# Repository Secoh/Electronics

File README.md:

# Electronics
Educational etudes related to electronics, schematics, PCB layout, etc.

Fairly random collection of designs related to my hobbies, with backup in hidden agenda.
Historic items are in PCB123 (private vendor-specific, incompatible with anything else); more recent work is KiCad and LtSpice.

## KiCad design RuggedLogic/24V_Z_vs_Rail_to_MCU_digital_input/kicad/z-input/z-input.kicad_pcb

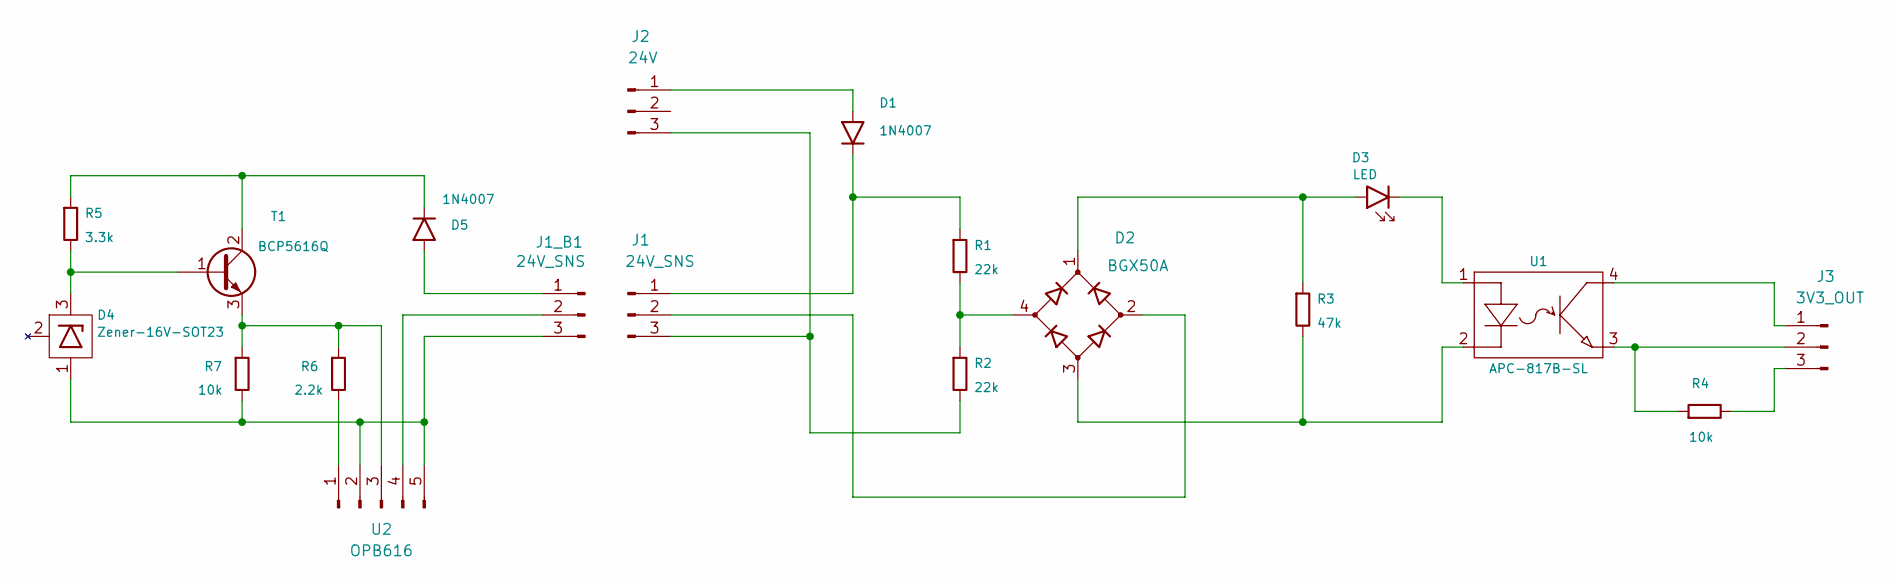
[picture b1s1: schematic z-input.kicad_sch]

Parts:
D1, D5: 1N4007; D_SOD-123F_hand_soldering
D2: BGX50A; SOT-143_Handsoldering
D3: LED; LED_0805
D4: Zener-16V-SOT23; SOT-23_Handsoldering
J1, J1_B1: 24V_SNS; Molex_KK-396_A-41791-0003_1x03_P3.96mm_Vertical
J2: 24V; Molex_KK-396_A-41791-0003_1x03_P3.96mm_Vertical
J3: 3V3_OUT; PinHeader_1x03_P2.54mm_Vertical
R1, R2: 22k; R_0805_2012Metric_Pad1.20x1.40mm_HandSolder
R3: 47k; R_0805_2012Metric_Pad1.20x1.40mm_HandSolder
R4, R7: 10k; R_0805_2012Metric_Pad1.20x1.40mm_HandSolder
R5: 3.3k; R_0805_2012Metric_Pad1.20x1.40mm_HandSolder
R6: 2.2k; R_0805_2012Metric_Pad1.20x1.40mm_HandSolder
T1: BCP5616Q; SOT-223-3_TabPin2
U1: APC-817B-SL; APC-817-SL
U2: OPB616; OPB-616

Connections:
unnamed: D1.2 (A), J2.1
unnamed: D1.1 (K), J1.1, R1.1
unnamed: D2.1 (+), D3.2 (A), R3.1
unnamed: D2.3 (-), R3.2, U1.2 (D-)
unnamed: D2.4, R1.2, R2.1
unnamed: D3.1 (K), U1.1 (D+)
unnamed: D4.1 (A), J1_B1.3, R7.2, U2.2, U2.5
unnamed: D4.3 (K), R5.2, T1.1 (B)
unnamed: D5.2 (A), J1_B1.1
unnamed: D5.1 (K), R5.1, T1.2 (C)
unnamed: D2.2, J1.2
unnamed: J1.3, J2.3, R2.2
unnamed: J1_B1.2, U2.4
unnamed: J3.1, U1.4 (C)
unnamed: J3.2, R4.1, U1.3 (C)
unnamed: J3.3, R4.2
unnamed: R6.1, R7.1, T1.3 (E), U2.3
unnamed: R6.2, U2.1

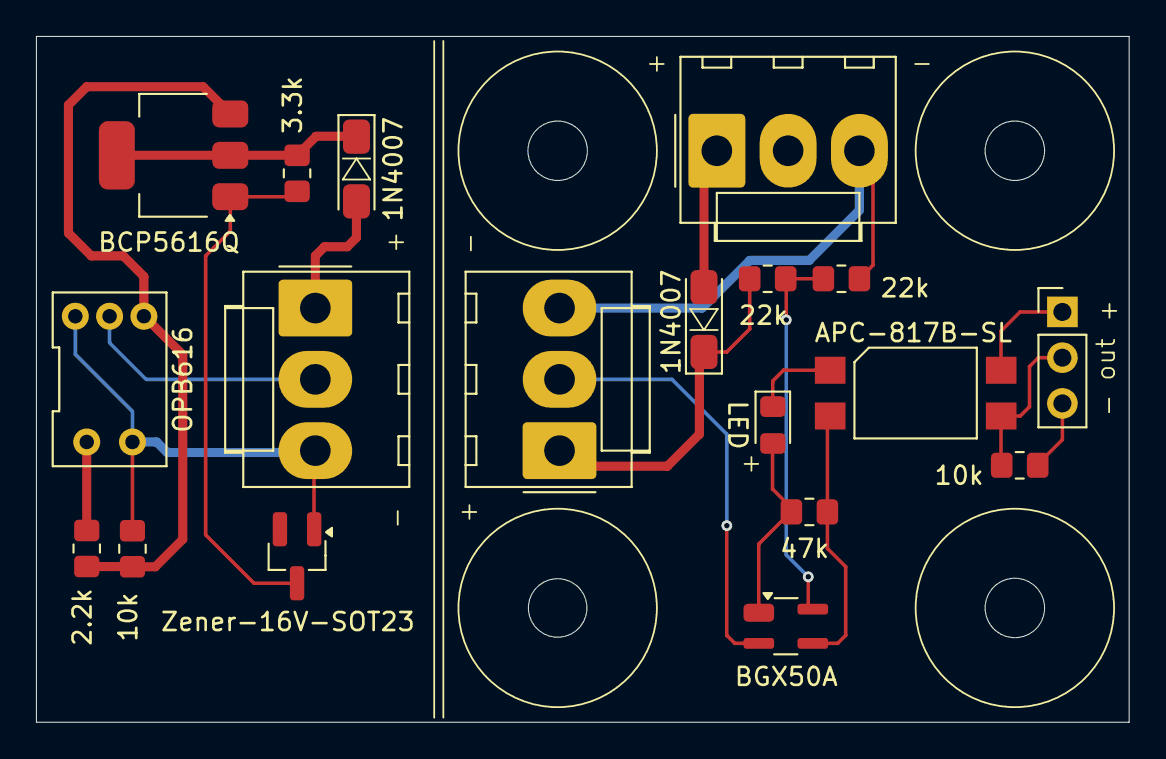
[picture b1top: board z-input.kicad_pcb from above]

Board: 2 copper layers, 60.7 x 38.1 mm, 19 parts (0 on the bottom side), 18 nets.

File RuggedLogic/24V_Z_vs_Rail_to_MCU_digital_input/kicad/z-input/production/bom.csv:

Designator,Footprint,Quantity,Value,LCSC Part #
"D1, D5",D_SOD-123F_hand_soldering,2,1N4007,
D2,SOT-143_Handsoldering,1,BGX50A,
D3,LED_0805,1,LED,
D4,SOT-23_Handsoldering,1,Zener-16V-SOT23,
"J1, J1_B1",Molex_KK-396_A-41791-0003_1x03_P3.96mm_Vertical,2,24V_SNS,
J2,Molex_KK-396_A-41791-0003_1x03_P3.96mm_Vertical,1,24V,
J3,PinHeader_1x03_P2.54mm_Vertical,1,3V3_OUT,
"R1, R2",0805,2,22k,
R3,0805,1,47k,
"R4, R7",0805,2,10k,
R5,0805,1,3.3k,
R6,0805,1,2.2k,
T1,SOT-223-3_TabPin2,1,BCP5616Q,
U1,APC-817-SL,1,APC-817B-SL,
U2,OPB-616,1,OPB616,

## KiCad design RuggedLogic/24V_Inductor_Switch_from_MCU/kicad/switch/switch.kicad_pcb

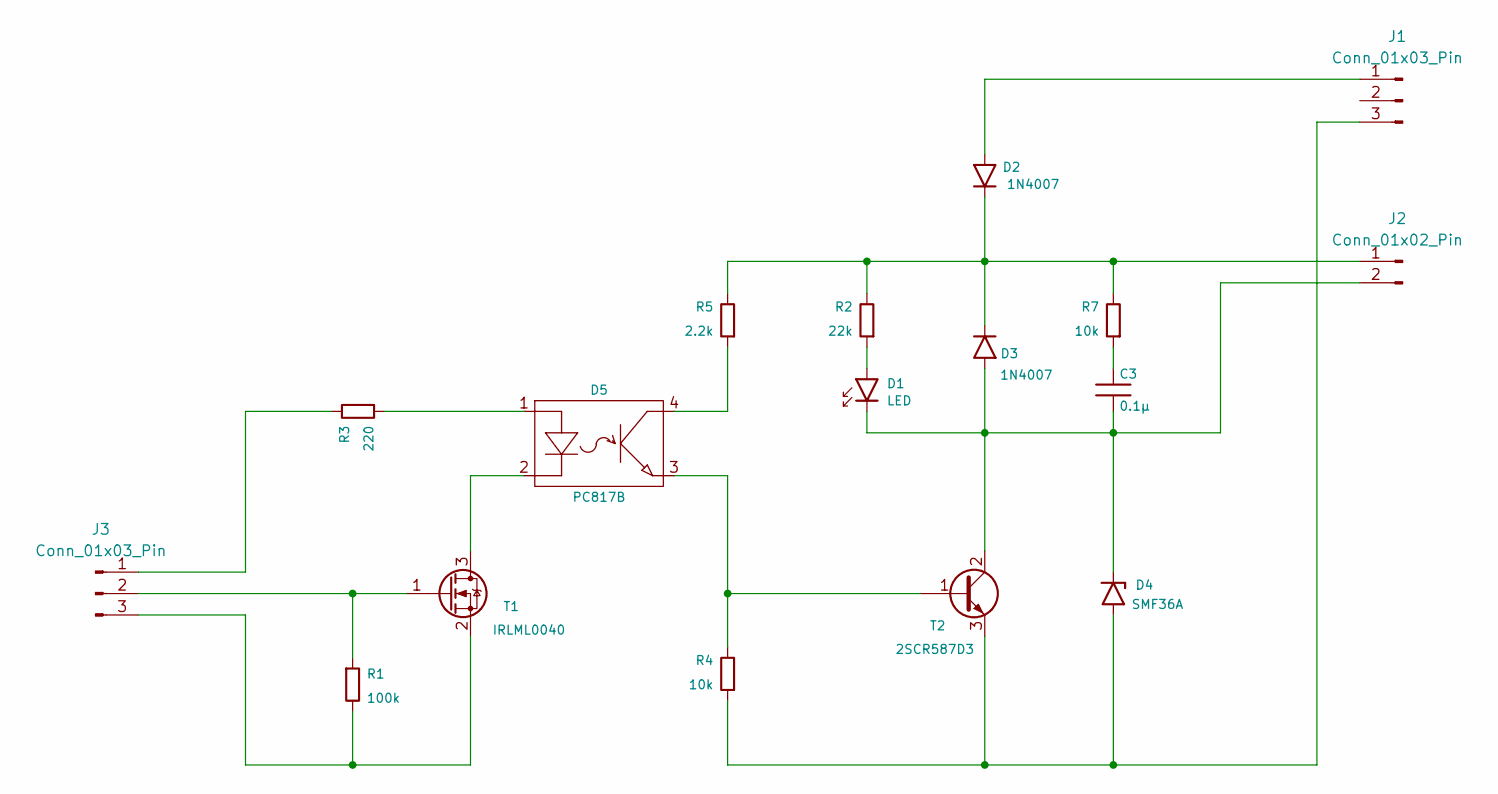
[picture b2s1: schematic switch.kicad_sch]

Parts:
C3: 0.1µ; C_0805_2012Metric_Pad1.18x1.45mm_HandSolder
D1: LED; LED_0805
D2, D3: 1N4007; D_SOD-123F_hand_soldering
D4: SMF36A; D_SOD-123F_hand_soldering
D5: PC817B; APC-817-SL
J1: Conn_01x03_Pin; Molex_KK-396_A-41791-0003_1x03_P3.96mm_Vertical
J2: Conn_01x02_Pin; Molex_KK-396_A-41791-0002_1x02_P3.96mm_Vertical
J3: Conn_01x03_Pin; PinHeader_1x03_P2.54mm_Vertical
R1: 100k; R_0805_2012Metric_Pad1.20x1.40mm_HandSolder
R2: 22k; R_0805_2012Metric_Pad1.20x1.40mm_HandSolder
R3: 220; R_0805_2012Metric_Pad1.20x1.40mm_HandSolder
R4, R7: 10k; R_0805_2012Metric_Pad1.20x1.40mm_HandSolder
R5: 2.2k; R_0805_2012Metric_Pad1.20x1.40mm_HandSolder
T1: IRLML0040; SOT-23_Handsoldering
T2: 2SCR587D3; TO-252-2

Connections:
unnamed: C3.1, R7.1
unnamed: D1.2 (A), R2.1
unnamed: C3.2, D1.1 (K), D3.2 (A), D4.1 (K), J2.2, T2.2 (C)
unnamed: D2.2 (A), J1.1
unnamed: D2.1 (K), D3.1 (K), J2.1, R2.2, R5.2, R7.2
unnamed: D4.2 (A), J1.3, R4.1, T2.3 (E)
unnamed: D5.4 (C), R5.1
unnamed: D5.1 (D+), R3.1
unnamed: D5.2 (D-), T1.3 (D)
unnamed: J3.1, R3.2
unnamed: J3.2, R1.1, T1.1 (G)
unnamed: J3.3, R1.2, T1.2 (S)
unnamed: D5.3 (C), R4.2, T2.1 (B)

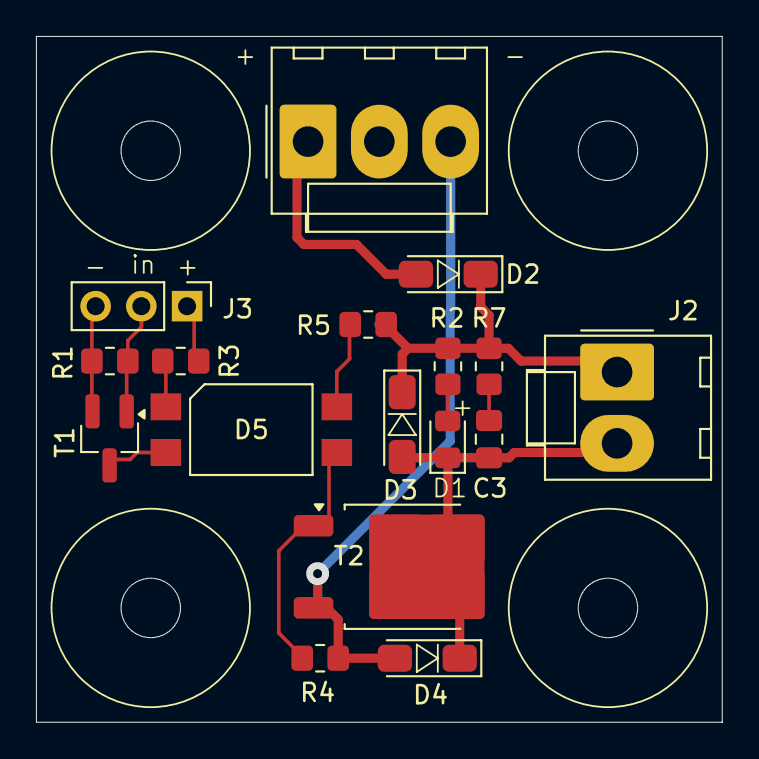
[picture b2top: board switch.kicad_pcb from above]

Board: 2 copper layers, 38.1 x 38.1 mm, 17 parts (0 on the bottom side), 13 nets.

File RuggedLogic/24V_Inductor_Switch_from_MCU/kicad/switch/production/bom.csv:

Designator,Footprint,Quantity,Value,LCSC Part #
C3,0805,1,0.1µ,
D1,LED_0805,1,LED,
"D2, D3",D_SOD-123F_hand_soldering,2,1N4007,
D4,D_SOD-123F_hand_soldering,1,SMF36A,
D5,APC-817-SL,1,PC817B,
J1,Molex_KK-396_A-41791-0003_1x03_P3.96mm_Vertical,1,Conn_01x03_Pin,
J2,Molex_KK-396_A-41791-0002_1x02_P3.96mm_Vertical,1,Conn_01x02_Pin,
J3,PinHeader_1x03_P2.54mm_Vertical,1,Conn_01x03_Pin,
R1,0805,1,100k,
R2,0805,1,22k,
R3,0805,1,220,
"R4, R7",0805,2,10k,
R5,0805,1,2.2k,
T1,SOT-23_Handsoldering,1,IRLML0040,
T2,TO-252-2,1,2SCR587D3,

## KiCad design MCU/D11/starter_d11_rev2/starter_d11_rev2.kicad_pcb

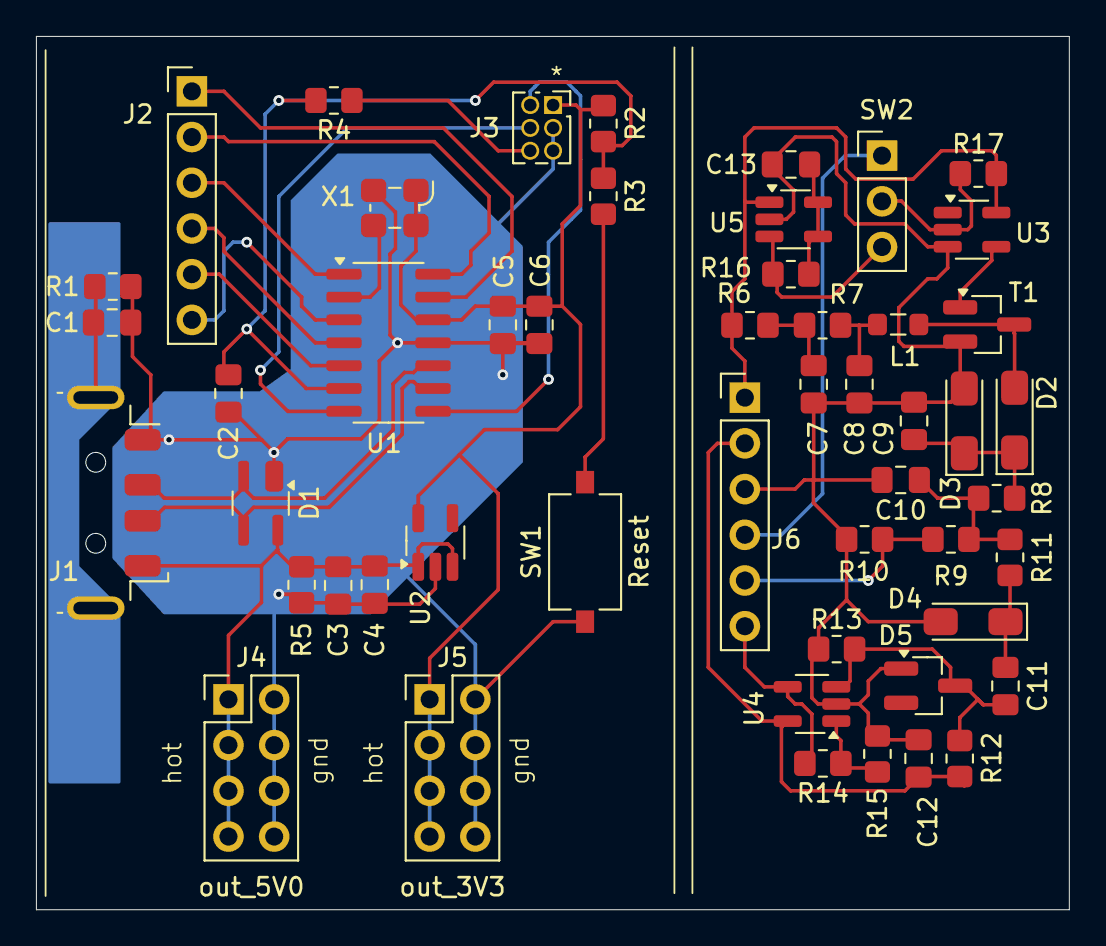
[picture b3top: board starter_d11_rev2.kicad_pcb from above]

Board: 2 copper layers, 57.4 x 48.5 mm, 52 parts (1 on the bottom side), 36 nets.

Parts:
C1, C2: 4.7n; C_0805_2012Metric_Pad1.18x1.45mm_HandSolder
C3, C6: 100n; C_0805_2012Metric_Pad1.18x1.45mm_HandSolder
C4, C5: 4.7u; C_0805_2012Metric_Pad1.18x1.45mm_HandSolder
C7, C8, C13: 2.2µ; C_0805_2012Metric_Pad1.18x1.45mm_HandSolder
C9, C10: 1µ; C_0805_2012Metric_Pad1.18x1.45mm_HandSolder
C11: 0.01µ; C_0805_2012Metric_Pad1.18x1.45mm_HandSolder
C12: 0.1µ; C_0805_2012Metric_Pad1.18x1.45mm_HandSolder
D1: PRTR5V0; SOT-143_Handsoldering
D2: 1N4007; D_SOD-123F_hand_soldering
D3: SMF36A; D_SOD-123F_hand_soldering
D4: SMF24A; D_SOD-123F_hand_soldering
D5: MMBZ5222BLT1G; SOT-23_Handsoldering
J1: USB_A; USB_A_Molex_48037-2200_Horizontal
J1A: USB; pad_single_005x036in_for_USB_A
J2, J6: Conn_01x06_Pin; PinHeader_1x06_P2.54mm_Vertical
J3: SWD-5; PinSocket_2x03_P1.27mm_Vertical
J4: out_5V0; PinHeader_2x04_P2.54mm_Vertical
J5: out_3V3; PinHeader_2x04_P2.54mm_Vertical
L1: 100µ; L_0805_2012Metric_Pad1.05x1.20mm_HandSolder
R1, R5: 1M; R_0805_2012Metric_Pad1.20x1.40mm_HandSolder
R2, R9, R11, R14, R17: 100k; R_0805_2012Metric_Pad1.20x1.40mm_HandSolder
R3, R4: 39; R_0805_2012Metric_Pad1.20x1.40mm_HandSolder
R6, R7: 33; R_0805_2012Metric_Pad1.20x1.40mm_HandSolder
R8, R10, R15: 10k; R_0805_2012Metric_Pad1.20x1.40mm_HandSolder
R12: 1Meg; R_0805_2012Metric_Pad1.20x1.40mm_HandSolder
R13: 47k; R_0805_2012Metric_Pad1.20x1.40mm_HandSolder
R16: 180; R_0805_2012Metric_Pad1.20x1.40mm_HandSolder
SW1: Reset; SW_Tactile_SPST_NO_Straight_CK_PTS636Sx25SMTRLFS
SW2: Conn_01x03_Pin; PinHeader_1x03_P2.54mm_Vertical
T1: 2N7002; SOT-23_Handsoldering
U1: ATSAMD11C14A-SS; SOIC-14_3.9x8.7mm_P1.27mm
U2: TLV73333/SOT-23; SOT-23-5_HandSoldering
U3: MC74VHC1GT14; SOT-23-5_HandSoldering
U4: MAX4230; SOT-23-5_HandSoldering
U5: MIC1555; SOT-23-5_HandSoldering
X1: ECS-2520MV-xxx-xx; ECS-2520MV

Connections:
3V3: C5.1, C6.1, J3.1, J5.1, J5.3, J5.5, J5.7, R2.1, U1.12 (VDD), U2.5 (3V3), X1.1 (Tri-State), X1.4 (VDD)
3V3-1: C12.1, J6.2, R12.1, U4.5 (V+)
5V0: C3.1, C4.1, D1.4 (Vcc), J1.1 (VBUS), J4.1, J4.3, J4.5, J4.7, R5.1, U2.1 (IN), U2.3 (EN)
5V0-1: J6.1, R6.2, R17.2, U3.5 (VCC), U5.1 (VCC)
/Inset A - USB MCU/CLK: U1.2 (PA08/XIN), X1.3 (OUT)
/Inset A - USB MCU/RST: C2.1, R2.2, R3.1, R4.2, U1.6 (PA28/~RST)
/Inset A - USB MCU/SWCLK: J3.4, U1.7 (PA30/SWCLK)
/Inset A - USB MCU/SWDIO: J3.2, U1.8 (PA31/SWDIO)
/Inset A - USB MCU/Shield: C1.1, J1.5 (Shield), J1A.1, R1.1
/Inset A - USB MCU/USB-M: D1.3, J1.2 (D-), U1.9 (PA24)
/Inset A - USB MCU/USB-P: D1.2, J1.3 (D+), U1.10 (PA25)
DRV: J6.4, SW2.1
GEN: J6.6, R14.2, U4.4
GND: C1.2, C2.2, C3.2, C4.2, C5.2, C6.2, D1.1 (Gnd), J1.4 (GND), J3.3, J3.5, J4.2, J4.4, J4.6, J4.8, J5.2, J5.4, J5.6, J5.8, R1.2, R5.2, SW1.1, U1.11 (GND), U2.2 (GND), X1.2 (GND)
GND1: C7.2, C8.2, C9.2, C10.2, C12.2, C13.2, D3.2 (A), D4.2 (A), D5.1 (A), J6.3, R10.1, R13.1, R15.2, T1.2 (S), U3.3 (GND), U4.2 (V-), U5.2 (GND)
unnamed: C7.1, R6.1, R7.2
unnamed: C8.1, L1.1, R7.1
unnamed: C10.1, R8.1, R9.2, R11.2
unnamed: D2.2 (A), L1.2, T1.3 (D)
unnamed: C9.1, D2.1 (K), D3.1 (K), R8.2
unnamed: C11.2, D4.1 (K), R11.1
unnamed: C11.1, D5.3 (K), R12.2, R13.2, U4.3 (-)
unnamed: J2.1, U1.13 (PA02)
unnamed: J2.2, U1.14 (PA04)
unnamed: J2.3, U1.1 (PA05)
unnamed: J2.4, U1.4 (PA14)
unnamed: J2.5, U1.5 (PA15)
unnamed: J2.6, U1.3 (PA09/XOUT)
unnamed: J3.6, R4.1
unnamed: R3.2, SW1.2
unnamed: R17.1, SW2.2, U3.2
unnamed: R16.1, SW2.3, U5.3 (OUT)
unnamed: T1.1 (G), U3.4
unnamed: R14.1, R15.1, U4.1 (+)
unnamed: C13.1, R16.2, U5.4 (TRG), U5.5 (THR)
RDY: J6.5, R9.1, R10.2

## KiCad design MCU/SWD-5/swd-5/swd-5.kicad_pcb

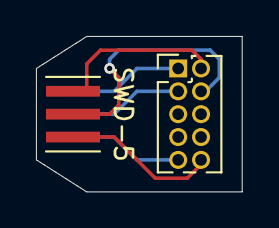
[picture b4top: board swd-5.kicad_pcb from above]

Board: 2 copper layers, 11.4 x 8.6 mm, 3 parts (1 on the bottom side), 6 nets.

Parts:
J1-A1, J1-B1: SWD-5; conn_edge_hdr_pin_3_spc_1.27
J2: SWD-10; PinHeader_2x05_P1.27mm_Vertical

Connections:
/GND: J1-A1.2, J2.3
/GND2: J1-A1.3, J2.9
/RST: J1-B1.3, J2.10
/SWCLK: J1-B1.2, J2.4
/SWDIO: J1-B1.1, J2.2
/VCC: J1-A1.1, J2.1

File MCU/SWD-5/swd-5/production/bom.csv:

Designator,Footprint,Quantity,Value,LCSC Part #
"J1-A1, J1-B1",conn_edge_hdr_pin_3_spc_1.27,2,SWD-5,
J2,PinHeader_2x05_P1.27mm_Vertical,1,SWD-10,

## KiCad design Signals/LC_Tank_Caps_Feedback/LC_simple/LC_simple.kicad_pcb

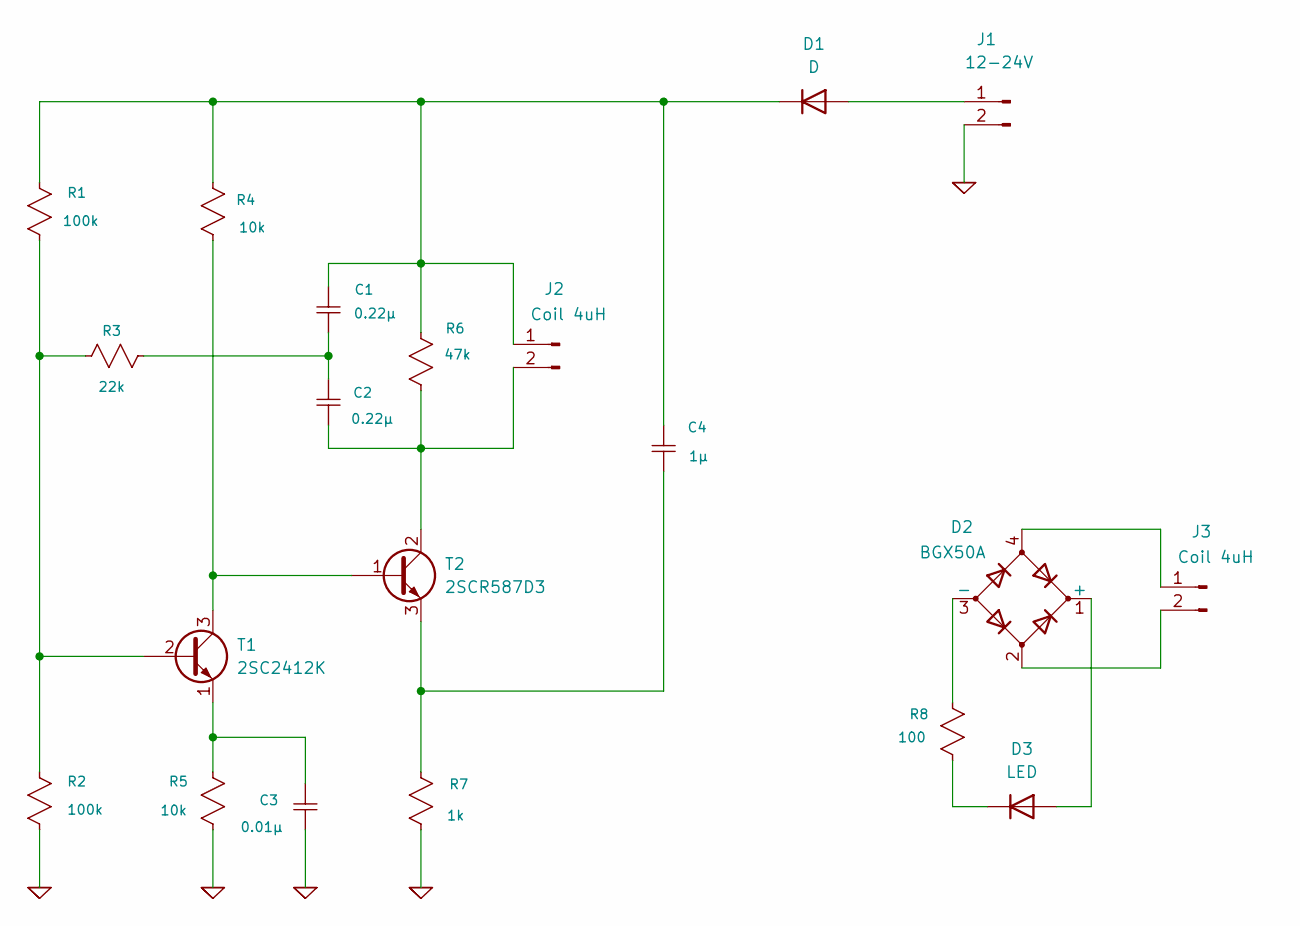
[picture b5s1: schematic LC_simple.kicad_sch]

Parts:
C1, C2: 0.22µ; C_0805_2012Metric_Pad1.18x1.45mm_HandSolder
C3: 0.01µ; C_0805_2012Metric_Pad1.18x1.45mm_HandSolder
C4: 1µ; C_0805_2012Metric_Pad1.18x1.45mm_HandSolder
D1: D; D_SOD-123F
D2: BGX50A; SOT-143_Handsoldering
D3: LED; LED_0805_2012Metric_Pad1.15x1.40mm_HandSolder
J1: 12-24V; Molex_KK-396_5273-02A_1x02_P3.96mm_Vertical
J2, J3: Coil 4uH; PinHeader_1x02_P2.54mm_Vertical
R1, R2: 100k; R_0805_2012Metric_Pad1.20x1.40mm_HandSolder
R3: 22k; R_0805_2012Metric_Pad1.20x1.40mm_HandSolder
R4, R5: 10k; R_0805_2012Metric_Pad1.20x1.40mm_HandSolder
R6: 47k; R_0805_2012Metric_Pad1.20x1.40mm_HandSolder
R7: 1k; R_0805_2012Metric_Pad1.20x1.40mm_HandSolder
R8: 100; R_0805_2012Metric_Pad1.20x1.40mm_HandSolder
T1: 2SC2412K; SOT-23_Mirrored_Handsoldering
T2: 2SCR587D3; TO-252-2

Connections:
0: C3.2, J1.2, R2.2, R5.2, R7.2
unnamed: C1.2, C2.1, R3.1
unnamed: D1.2 (A), J1.1
unnamed: C1.1, C4.1, D1.1 (K), J2.1, R1.1, R4.1, R6.1
unnamed: D2.1 (+), D3.2 (A)
unnamed: D2.3 (-), R8.1
unnamed: D3.1 (K), R8.2
unnamed: C2.2, J2.2, R6.2, T2.2 (C)
unnamed: D2.4, J3.1
unnamed: D2.2, J3.2
unnamed: R1.2, R2.1, R3.2, T1.2 (B)
unnamed: R4.2, T1.3 (C), T2.1 (B)
unnamed: C3.1, R5.1, T1.1 (E)
unnamed: C4.2, R7.1, T2.3 (E)

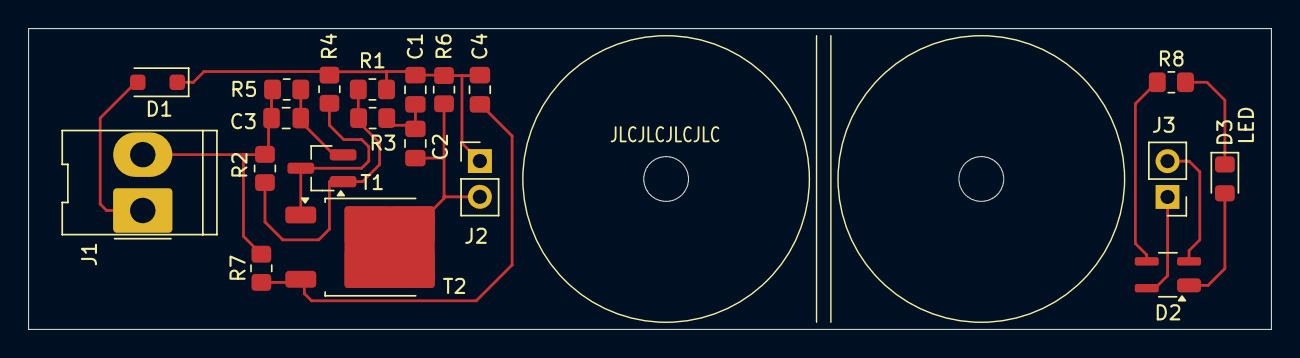
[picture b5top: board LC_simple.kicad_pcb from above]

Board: 2 copper layers, 88.1 x 21.3 mm, 20 parts (0 on the bottom side), 14 nets.

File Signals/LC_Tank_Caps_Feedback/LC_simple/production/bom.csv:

Designator,Footprint,Quantity,Value,LCSC Part #
"C1, C2",0805,2,0.22µ,
C3,0805,1,0.01µ,
C4,0805,1,1µ,
D1,D_SOD-123F,1,D,
D2,SOT-143_Handsoldering,1,BGX50A,
D3,0805,1,LED,
J1,Molex_KK-396_5273-02A_1x02_P3.96mm_Vertical,1,12-24V,
"J2, J3",PinHeader_1x02_P2.54mm_Vertical,2, Coil 4uH,
"R1, R2",0805,2,100k,
R3,0805,1,22k,
"R4, R5",0805,2,10k,
R6,0805,1,47k,
R7,0805,1,1k,
R8,0805,1,100,
T1,SOT-23_Mirrored_Handsoldering,1,2SC2412K,
T2,TO-252-2,1,2SCR587D3,

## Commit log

2024-05-29 Initial upload
2024-05-30 more PWM current source modeling
2024-05-31 Electronics: Low side switch, PWM variants
2024-06-01 PWM full tract one wing
2024-06-12 simplify noise generator
2024-06-16 Redone Z-input PCB; production update
2024-06-18 D11 project is split into pages Transistors updated in PWM and Thyristor
2024-06-25 D11 schematics and PCB updates - printed prototype version
2024-06-30 Fixed errors in Rugged Z sensor Fixes to Rugged Switch
2024-06-30 Updated Rugged Z sensor and Switch; schematics and PCB
